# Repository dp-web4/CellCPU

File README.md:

# CellCPU Documentation

**ModBatt Battery Management System - Individual Cell Controller**

## Overview

The CellCPU is a **production-ready** foundational component of ModBatt's hierarchical battery management system, providing individual cell monitoring and control for lithium-ion battery applications. Each CellCPU manages a single cell with precision voltage monitoring, temperature sensing, and active balancing control.

**Implementation Status**: ✅ **Complete and functional** - All core modules implemented with sophisticated interrupt-driven architecture.

### Quick Facts

- **Target Platform**: ATtiny45 microcontroller (8-bit AVR)
- **Cell Interface**: Direct monitoring of single lithium-ion cell
- **Temperature Sensor**: MCP9843 precision digital sensor
- **Communication**: Virtual UART at 20kbps in daisy-chain topology
- **Power Consumption**: <1mA typical operation
- **Scalability**: Up to 128 CellCPUs per ModuleCPU

## Web4 Ecosystem Context

CellCPU is the foundational layer of a **trust-native battery management system** demonstrating [Web4](https://github.com/dp-web4/web4) principles in production embedded hardware:

**Philosophy**: [Synchronism](https://github.com/dp-web4/Synchronism) - Distributed intelligence and scale-based autonomy
**Standard**: [Web4](https://github.com/dp-web4/web4) - Trust-native internet architecture with LCTs and MRH
**Implementation**: **CellCPU** (this) → [ModuleCPU](https://github.com/dp-web4/ModuleCPU) → [Pack-Controller](https://github.com/dp-web4/Pack-Controller-EEPROM)

### Web4 Integration

Each CellCPU operates as an autonomous agent with:
- **LCT Identity**: Unforgeable blockchain binding via hardware serial number
- **Markov Blanket**: VUART interface hides internal complexity from ModuleCPU
- **Local Intelligence**: Autonomous decision-making (balancing, error detection)
- **Trust Tensors**: ModuleCPU tracks T3 (Talent/Training/Temperament) and V3 (Veracity/Validity/Value)
- **Witnessed Presence**: ModuleCPU witnesses cell existence via VUART communication

See [WEB4_INTEGRATION.md](WEB4_INTEGRATION.md) for complete Web4 architecture details.

### Synchronism Principles

CellCPU demonstrates cosmic-to-silicon philosophy:
- **Scale-Based Autonomy**: Cell makes local decisions within module context
- **Markov Blankets**: VUART interface defines cell's reality boundary
- **Distributed Intelligence**: No central cell controller - intelligence emerges from hierarchy
- **Sensor Fusion**: Temperature + voltage + time → emergent "cell health"
- **Intent Dynamics**: Battery charge/discharge as metabolic intent propagation

See [SYNCHRONISM_PRINCIPLES.md](SYNCHRONISM_PRINCIPLES.md) for philosophical depth.

### Ecosystem Links

- [Synchronism Whitepaper](https://github.com/dp-web4/Synchronism/blob/main/whitepaper.md) - Universal principles
- [Web4 Standard](https://github.com/dp-web4/web4/blob/main/web4-standard/README.md) - Internet standard
- [ModBatt Web4 Examples](https://github.com/dp-web4/web4/blob/main/docs/modbatt_implementation_examples.md) - Code walkthroughs

**This is not just a battery controller - it's proof that Web4 trust architecture works in 4KB of flash memory.**

---

## Documentation Structure

### 📖 Core Documentation

#### [System Overview](docs/overview/README.md)
Complete system overview, architecture, and integration context within the ModBatt ecosystem.

- System role and responsibilities
- Hardware platform specifications  
- Communication protocol overview
- Performance characteristics
- Integration with ModuleCPU and Pack Controller

#### [Software Architecture](docs/overview/architecture.md)
Detailed firmware architecture and design patterns.

- Event-driven state machine design
- Module organization and dependencies
- Memory management strategies
- Interrupt architecture
- Error handling and safety systems

### 🔧 Hardware Documentation

#### [Hardware Platform](docs/hardware/README.md)
Comprehensive hardware platform documentation covering the ATtiny45 microcontroller and supporting components.

- ATtiny45 specifications and capabilities
- Pin configuration and multiplexing
- External component integration
- Power system design
- PCB layout considerations
- Environmental specifications

### 💻 Firmware Documentation

#### [Firmware Architecture](docs/firmware/README.md)
Complete firmware module documentation and implementation details.

- Module hierarchy and interfaces
- ADC voltage measurement system
- Virtual UART communication implementation
- Temperature sensor integration
- Platform abstraction layer
- Build system and optimization

#### [Cell Interface & Monitoring](docs/cell-interface/README.md)
Detailed cell monitoring and control system documentation.

- Voltage monitoring with 10-bit ADC
- Temperature sensing via I2C
- Active balancing control
- Safety and protection features
- Calibration and accuracy optimization
- Diagnostic capabilities

### 🔗 Communication System

#### [Communication with ModuleCPU](docs/communication/README.md)
Complete communication protocol and implementation documentation.

- Physical layer implementation
- Message format and structure
- Daisy-chain topology management
- Virtual UART timing and control
- Error handling and recovery
- Performance optimization

#### [Temperature Sensing](docs/temperature/README.md)
Comprehensive temperature monitoring system documentation.

- MCP9843 sensor integration
- I2C communication interface
- Thermal management and control
- Pin multiplexing with ADC
- Calibration and accuracy
- Error handling and diagnostics

### 🛠️ Development

#### [Development Environment](docs/development/README.md)
Complete development environment setup and workflow documentation.

- Required software tools (Microchip Studio, XC8)
- Hardware setup and programming
- Build process and optimization
- Testing and validation procedures
- Version control workflow
- Best practices and standards

#### [Implementation Status](docs/implementation-status.md)
**NEW**: Comprehensive review of actual implementation completeness and quality.

- Complete module implementation status
- Code quality assessment
- Production readiness evaluation
- Hardware validation priorities
- Integration testing recommendations

## Quick Start Guide

### 1. Development Environment Setup

```bash
# Required Tools
1. Download and install Microchip Studio 7.0+
2. Install XC8 Compiler v2.36+
3. Setup Atmel-ICE programmer/debugger
4. Clone the CellCPU repository

# Open Project
1. Launch Microchip Studio
2. File → Open → Project/Solution
3. Select CellCPU.cproj
4. Build → Build Solution (F7)
```

### 2. Hardware Configuration

```c
// Key hardware connections
Pin Configuration:
├── PB0: cell_up_tx    (Output to upstream cell)
├── PB1: cell_dn_rx    (Input from downstream)
├── PB2: I2C SDA       (Temperature sensor)
├── PB3: I2C SCL/ADC3  (Temperature + voltage)
├── PB4: cell_up_rx    (Input from upstream)
└── PB5: cell_dn_tx    (Output to downstream)

Power: 3.0V to 5.5V (5.0V nominal)
Programming: 6-pin ISP header
```

### 3. Basic Usage

```c
// Actual implemented functionality
System Operation:
1. Interrupt-driven Virtual UART communication (20kbps)
2. Pin-multiplexed voltage (ADC) and temperature (I2C) sensing
3. MCP9843 EVENT pin control for discharge balancing
4. Sophisticated timer-based bit timing with guard bits
5. Automatic chain position detection and data relay
6. Robust I2C bit-banged implementation with ACK handling
7. Power-efficient ADC enable/disable cycling

// Core modules all implemented:
├── adc.c - Complete ADC implementation with power management
├── I2c.c - Full bit-banged I2C with timing quantization  
├── mcp9843.c - Complete temperature sensor driver
├── vUART.c - Sophisticated interrupt-driven communication
└── main.c - Complete state machine coordination
```

## Key Features

### 🔋 Cell Monitoring
- **Voltage**: 10-bit ADC with 1.1V reference, ~4.3mV resolution
- **Temperature**: MCP9843 sensor, ±0.5°C accuracy, 0.0625°C resolution
- **Range**: 2.0V-5.0V cell voltage, -40°C to +125°C temperature

### 📡 Communication
- **Protocol**: Custom serial over Virtual UART
- **Speed**: 20kbps (50μs bit time)
- **Topology**: Daisy-chain up to 128 cells
- **Latency**: <5ms per cell response time

### ⚡ Control & Safety
- **Balancing**: Active discharge via MCP9843 EVENT pin
- **Protection**: Voltage and temperature limit monitoring
- **Safety**: Fail-safe operation on communication loss
- **Power**: <1mA typical, <100μA idle

### 🎯 Performance
- **Memory**: 4KB Flash (62% used), 256B SRAM (58% used)
- **Real-time**: Interrupt-driven with timer-based precision timing
- **Communication**: Sophisticated Virtual UART with guard bits and relay
- **I2C Implementation**: Professional bit-banged with timing quantization
- **Power Management**: ADC power cycling, efficient pin multiplexing
- **Reliability**: Comprehensive error handling and recovery mechanisms

## System Integration

### ModBatt Architecture Context

```
Vehicle Control Unit (VCU)
    ↓ CAN Bus
Pack Controller (STM32WB55)
    ↓ CAN Bus
ModuleCPU (ATmega64M1) ←→ Up to 128 × CellCPU (ATtiny45)
    ↓                              ↓
Battery Module                Li-ion Cells
```

### Communication Flow

```
Command Flow (Downstream):
ModuleCPU → CellCPU(Last) → CellCPU(Middle) → CellCPU(First)

Data Flow (Upstream):  
ModuleCPU ← CellCPU(Last) ← CellCPU(Middle) ← CellCPU(First)
```

## Contributing

### Development Workflow

1. **Feature Development**: Create feature branch from `develop`
2. **Code Review**: Submit pull request with comprehensive testing
3. **Integration**: Merge to `develop` after approval
4. **Release**: Create release branch for final testing
5. **Production**: Merge to `main` and tag release

### Coding Standards

- **Style**: K&R brace style, 4-space indentation
- **Documentation**: Comprehensive function headers and inline comments
- **Testing**: Unit tests and integration validation required
- **Performance**: Memory and timing optimization mandatory

## License and Patents

### Software License

This software is licensed under the **GNU Affero General Public License v3.0 or later** (AGPL-3.0-or-later).

See [LICENSE](LICENSE) for full license text.
See [LICENSE_SUMMARY.md](LICENSE_SUMMARY.md) for a summary of software vs. hardware licensing.

### Patents

Protected by US Patents:
- **11,380,942**: Distributed battery management with autonomous cell controllers
- **11,469,470**: Hierarchical battery management architecture
- **11,575,270**: Related pack control systems

**Patent Grant**: A limited patent grant for the software is provided under the AGPL-3.0 license scope. See [PATENTS.md](PATENTS.md) for details.

**Hardware Licensing**: Separate from software. See `docs/legal/ModBatt_Product_License.pdf` for hardware manufacturing licensing.

### Copyright

© 2023-2025 Modular Battery Technologies, Inc.

**Open Source Release**: October 2025 - Part of the Web4 trust-native ecosystem demonstration.

## Support and Contact

For technical support, development questions, or collaboration opportunities:

- **Technical Documentation**: See individual module documentation
- **Development Issues**: Check troubleshooting sections in relevant docs
- **Hardware Support**: Refer to hardware platform documentation
- **Communication Protocol**: See communication system documentation

---

## Related Projects

This repository can be viewed as demonstrating patterns of distributed trust and verifiable provenance in embedded systems.

**Related**: [Web4](https://github.com/dp-web4/web4) (trust architecture) • [Synchronism](https://github.com/dp-web4/Synchronism) (conceptual framing)

---

**Note**: This documentation covers the CellCPU firmware component of the ModBatt battery management system. For complete system documentation, refer to the Pack Controller and ModuleCPU documentation.

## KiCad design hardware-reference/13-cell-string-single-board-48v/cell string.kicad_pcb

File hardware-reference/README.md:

# CellCPU Hardware Reference Designs

**Status**: Reference designs for educational and non-commercial use
**Patent Coverage**: Protected by US Patent 11,380,942 (Distributed battery management with autonomous cell controllers)
**Last Updated**: October 2025

---

## Overview

This directory contains reference hardware designs for implementing the CellCPU concept - an autonomous cell-level battery management controller based on ATtiny45. These designs demonstrate one possible hardware implementation of the patented distributed battery management architecture.

**Contents**:
- KiCad schematics and PCB layouts
- Bill of Materials (BOM)
- Manufacturing files

---

## Patent Coverage

These hardware designs implement concepts covered by multiple patents in the ModBatt patent portfolio:

### Complete Patent List

**Modular Battery Technologies, Inc. Patent Portfolio**:

1. **US 11,380,942** (PCT/US21/50518) - *High Voltage Battery Module with Series Connected Cells and Internal Relays*
   - Filed: November 2, 2020 | Issued: July 5, 2022
   - Module with series connected cells and relays

2. **US 11,469,470** (PCT/US21/53798) - *Battery Module with Series Connected Cells, Internal Relays and Internal Battery Management System*
   - Filed: January 4, 2021 | Issued: October 11, 2022
   - Cell monitoring/conditioning circuit, PCBAs, methods

3. **US 11,563,241** - *Apparatus and Methods for Removable Battery Module with Internal Relay and Internal Controller*
   - Filed: February 10, 2021 | Issued: December 14, 2022
   - Authentication methods and circuits

4. **US 11,575,270** (PCT/US21/55047) - *Battery Module with Series Connected Cells, Internal Relays and Internal Battery Management System*
   - Filed: February 22, 2021 (CIP) | Issued: February 7, 2023
   - AC coupled comms and methods

5. **US 11,699,817** (PCT/US21/54434) - *Apparatus and Methods for Removable Battery Module with Internal Relay and Internal Controller*
   - Filed: March 31, 2021 | Issued: July 11, 2023
   - System, pack and module controllers, blockchain

6. **US 11,477,027** (PCT/US21/55813) - *Apparatus and Methods for Management of Controlled Objects*
   - Filed: May 11, 2021 | Issued: October 18, 2022
   - Multi-domain management of controlled objects, LCT/blockchain

7. **US 11,936,008** (PCT/US21/60860) - *Electrical Power System with Removable Battery Modules*
   - Filed: November 17, 2021 | Issued: March 19, 2024
   - Dissimilar modules in parallel

8. **US 12,278,913** (PCT/US22/24797) - *Apparatus and Methods for Management of Controlled Objects*
   - Filed: March 31, 2022 | Issued: April 15, 2025
   - Linking of identifiable records

9. **US 11,876,250** (PCT/US22/xxx) - *High Voltage Battery Module with Series Connected Cells and Internal Relays*
   - Filed: May 31, 2022 | Issued: January 16, 2024
   - Dissimilar relays, PLC control bus, linear and PWM modes

10. **US 12,046,722** - *Electrical Power System with Removable Battery Modules*
    - Filed: December 12, 2022 | Issued: July 23, 2024
    - Vehicle and stationary installations having a power system, energizing a bus

11. **US 12,405,309** - *Low Cost Battery Cell Monitoring Circuit*
    - Filed: January 3, 2023 | Issued: September 2, 2025
    - Low cost ASIC

12. **US 12,136,739** - *Low Cost Battery Cell Monitoring Circuit*
    - Filed: December 14, 2023 | Issued: November 5, 2024
    - Low cost ASIC methods

13. **US 12,142,737** - *Electrical Power System with Removable Battery Modules*
    - Filed: December 14, 2023 | Issued: November 12, 2024

14. **US 18/935,265** - *High Voltage Battery Module with 1-Phase and 3-Phase AC Output*
    - Filed: November 1, 2024 | Status: Pending

**Assignee**: Modular Battery Technologies, Inc.
**Inventors**: Dennis Palatov, et al.

### Key Patented Concepts in CellCPU Hardware

- Cell-level autonomous controllers with local intelligence
- Virtual UART communication in daisy-chain topology
- Distributed temperature and voltage monitoring
- Markov blanket interface hiding internal cell complexity
- Low-cost cell monitoring circuits and ASICs
- Authentication methods for cell controllers

---

## License and Usage Terms

### Software License
The **CellCPU firmware** (parent directory) is licensed under **AGPL-3.0-or-later** with a patent grant for software use. See `../LICENSE` for details.

### Hardware Reference Designs
These hardware reference designs are provided under the following terms:

#### ✅ Permitted Uses (Non-Commercial Patent Grant)

You MAY use these designs **without a commercial hardware license** for:

1. **Educational Use**: Academic research, teaching, and learning
2. **Personal/Hobby Use**: Individual projects and experimentation
3. **Research & Development**: Prototyping and testing new concepts
4. **Open Source Development**: Contributing to AGPL-licensed software improvements

**Conditions**:
- No commercial sale or distribution of manufactured hardware
- Acknowledge patent and provide attribution
- Derivative works must include similar non-commercial use notice
- Software modifications must comply with AGPL-3.0-or-later

#### ❌ Restricted Uses (Requires Commercial License)

You MUST obtain a commercial hardware license from Modular Battery Technologies, Inc. for:

1. **Commercial Manufacturing**: Producing hardware for sale
2. **Commercial Products**: Incorporating designs into commercial battery products
3. **Revenue Generation**: Any use where hardware generates revenue directly or indirectly
4. **OEM Integration**: Selling products that include these designs

**Contact**: For commercial licensing inquiries, contact Modular Battery Technologies, Inc.

---

## Technical Scope

These reference designs demonstrate:

- **Cell Controller**: ATtiny45-based autonomous controller per cell
- **Temperature Sensing**: MCP9843 I²C temperature sensor integration
- **Virtual UART**: Software-based serial communication at 20kbps
- **Daisy-Chain Topology**: Up to 128 cells in series connection
- **Voltage Monitoring**: Per-cell voltage measurement architecture
- **Relay Control**: Cell bypass/isolation relay interface

**Voltage Range**: Designed for 13-cell strings (48V nominal LiFePO4)

---

## AS-IS Disclaimer and Limitations

### ⚠️ NO WARRANTY

**THESE HARDWARE REFERENCE DESIGNS ARE PROVIDED "AS IS" WITHOUT WARRANTY OF ANY KIND, EXPRESS OR IMPLIED, INCLUDING BUT NOT LIMITED TO THE WARRANTIES OF MERCHANTABILITY, FITNESS FOR A PARTICULAR PURPOSE, TITLE, AND NON-INFRINGEMENT.**

### Specific Disclaimers

1. **No Guarantee of Functionality**: These designs may contain errors, omissions, or may not function as intended
2. **No Safety Certification**: Designs have NOT been certified for safety (UL, CE, etc.)
3. **High Voltage Hazard**: Battery systems operate at dangerous voltages - **risk of electric shock, fire, explosion**
4. **Chemical Hazard**: Lithium battery failures can cause fire, toxic fumes, and explosions
5. **No Professional Engineering Review**: Use at your own risk - consult qualified professionals
6. **Rapidly Evolving**: These designs may be outdated or superseded

### 🚨 Battery Safety Warning

**DANGER**: Lithium-ion and LiFePO4 batteries are potentially hazardous.

- **Thermal runaway** can cause fires and explosions
- **Improper charging** can cause battery damage and fire
- **Short circuits** can cause severe burns and fire
- **Cell imbalance** can reduce lifespan and create safety hazards

**You are solely responsible for:**
- Proper safety engineering and testing
- Compliance with electrical codes and regulations
- Fire suppression and containment systems
- Proper charging and monitoring equipment
- Insurance and liability coverage

---

## Limitation of Liability

**IN NO EVENT SHALL MODULAR BATTERY TECHNOLOGIES, INC., ITS AFFILIATES, OR CONTRIBUTORS BE LIABLE FOR ANY DIRECT, INDIRECT, INCIDENTAL, SPECIAL, EXEMPLARY, OR CONSEQUENTIAL DAMAGES (INCLUDING, BUT NOT LIMITED TO, PROCUREMENT OF SUBSTITUTE GOODS OR SERVICES; LOSS OF USE, DATA, OR PROFITS; BUSINESS INTERRUPTION; PROPERTY DAMAGE; PERSONAL INJURY; OR DEATH) HOWEVER CAUSED AND ON ANY THEORY OF LIABILITY, WHETHER IN CONTRACT, STRICT LIABILITY, OR TORT (INCLUDING NEGLIGENCE OR OTHERWISE) ARISING IN ANY WAY OUT OF THE USE OF THESE DESIGNS, EVEN IF ADVISED OF THE POSSIBILITY OF SUCH DAMAGE.**

---

## Regulatory Compliance

### Your Responsibility

If you manufacture hardware based on these designs, YOU are responsible for:

1. **Electrical Safety**: UL/CSA/CE compliance as required
2. **FCC/EMC Compliance**: Radio frequency emissions and immunity
3. **Environmental**: RoHS, REACH, WEEE directives
4. **Transportation**: UN38.3 battery shipping requirements (if applicable)
5. **Local Codes**: Electrical codes and building codes in your jurisdiction

### No Compliance Warranty

**These designs have NOT been tested for regulatory compliance.** You must perform your own testing and certification.

---

## Design Files Information

### KiCad Version
Designs created with KiCad EDA (exact version in `.kicad_pro` files)

### File Structure
- `.kicad_sch` - Schematic files (hierarchical sheets)
- `.kicad_pcb` - PCB layout files
- `.csv` / `.ods` - Bill of Materials
- `mfg/` - Manufacturing output files (Gerbers, drill files, pick-and-place)

### Viewing and Editing
1. Download and install KiCad: https://www.kicad.org/
2. Open `.kicad_pro` project file
3. Libraries may need to be remapped on first open

---

## Attribution and Derivative Works

If you create derivative works based on these designs:

1. **Acknowledge the Source**:
   ```
   Based on CellCPU hardware reference designs
   Copyright (c) 2024-2025 Modular Battery Technologies, Inc.
   https://github.com/dp-web4/CellCPU
   ```

2. **Maintain Patent Notice**: Include reference to ModBatt patent portfolio (see Patent Coverage section)

3. **Propagate Non-Commercial Terms**: If distributing derivatives, include similar non-commercial use restrictions

4. **No Endorsement**: Do not imply that your derivative work is endorsed by Modular Battery Technologies, Inc.

---

## Support and Contributions

### No Support Commitment
These reference designs are provided without support. No assistance is guaranteed.

### Community Contributions
Improvements to these reference designs are welcome via pull requests:
- Clearly document changes and reasoning
- Maintain safety-critical design margins
- Include SPDX license headers if adding new files
- Sign-off on contributions (Developer Certificate of Origin)

---

## Relationship to Software License

**Key Distinction**:
- **Software (CellCPU firmware)**: AGPL-3.0-or-later with broad patent grant for software use
- **Hardware (these designs)**: Non-commercial patent grant only; commercial use requires separate license

**Why the Difference?**
- Software improvements benefit the ecosystem when shared (AGPL ensures sharing)
- Hardware manufacturing involves significant capital investment and safety liability
- Patent coverage primarily relates to hardware architecture and topology

**Can I modify the software for use on different hardware?**
- Yes! The AGPL-3.0 software license and patent grant apply to the software
- You can run modified CellCPU software on your own hardware implementations
- Commercial hardware sales still require a hardware patent license

---

## Questions?

**Technical Questions**: Open an issue on GitHub (https://github.com/dp-web4/CellCPU/issues)
**Commercial Licensing**: Contact Modular Battery Technologies, Inc.
**Safety Concerns**: Consult a qualified electrical engineer and safety professional

---

## Legal Summary

| **Aspect** | **Terms** |
|------------|-----------|
| **Software License** | AGPL-3.0-or-later (see `../LICENSE`) |
| **Hardware Designs** | Reference only - non-commercial patent grant |
| **Patents** | 14 US patents (1 pending) - commercial use requires license |
| **Warranty** | NONE - "AS IS" |
| **Liability** | User assumes all risk and liability |
| **Safety** | NOT certified - dangerous high voltage battery application |
| **Commercial Use** | Requires separate commercial license agreement |

---

**© 2024-2025 Modular Battery Technologies, Inc.**
**Patents**: 14 US patents covering battery management systems (see Patent Coverage section)
**Reference designs provided for educational and non-commercial use only**

---

*Last updated: October 2025*
*For latest terms, see https://github.com/dp-web4/CellCPU*

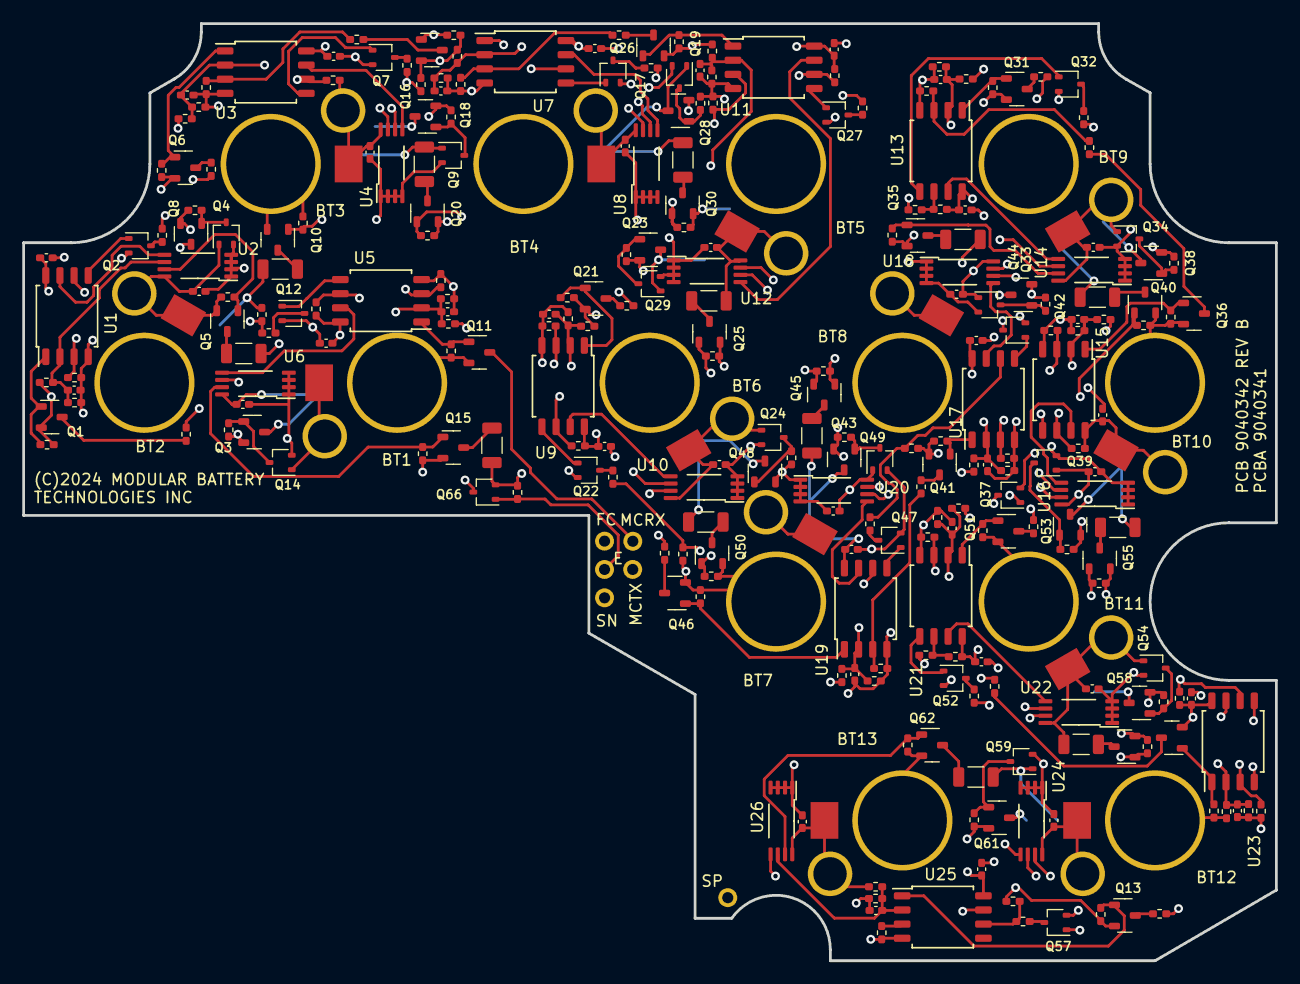
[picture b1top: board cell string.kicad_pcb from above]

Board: 4 copper layers, 112.5 x 84.2 mm, 275 parts (0 on the bottom side), 168 nets.

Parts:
BT1, BT2, BT3, BT4, BT5, BT6, BT7, BT8, BT9, BT10, BT11, BT12, BT13: Battery_Cell; modbatt cell new
C1, C3, C4, C6, C7, C9, C10, C12, C13, C15, C16, C18, C19, C21, C22, C24, C25, C27, C28, C30, C31, C33, C34, C36, C37, C39: .1uF; C_0402_1005Metric_Pad0.74x0.62mm_HandSolder
C2, C5, C8, C11, C14, C17, C20, C23, C26, C29, C32, C35, C38: 10pF; C_0402_1005Metric_Pad0.74x0.62mm_HandSolder
J1, J2, J3, J4, J5, J6: Conn_01x01_Pin; PinHeader_1x01_P1.00mm_Horizontal
Q1, Q3, Q5, Q6, Q8, Q10, Q11, Q13, Q15, Q16, Q18, Q20, Q21, Q23, Q25, Q26, Q28, Q30, Q31, Q33, Q35, Q36, Q38, Q40, Q41, Q43, Q45, Q46, Q48, Q50, Q51, Q53, Q55, Q56, Q58, Q60, Q61, Q62: DMP3099L-7-HXY; SOT-23
Q2, Q4, Q7, Q9, Q12, Q14, Q17, Q19, Q22, Q24, Q27, Q29, Q32, Q34, Q37, Q39, Q42, Q44, Q47, Q49, Q52, Q54, Q57, Q59, Q66: 2N7002; SOT-323_SC-70
R1, R2, R3, R4, R5, R8, R11, R12, R13, R14, R15, R18, R21, R22, R23, R24, R25, R31, R32, R33, R34, R35, R38, R41, R42, R43, R44, R45, R48, R51, R52, R53, R54, R55, R58, R61, R62, R63, R64, R65, R68, R71, R72, R73, R74, R75, R78, R81, R82, R83, R84, R85, R88, R91, R92, R93, R94, R95, R98, R101, R102, R103, R104, R105, R108, R111, R112, R113, R114, R115, R118, R121, R122, R131: 2.2K; R_0402_1005Metric_Pad0.72x0.64mm_HandSolder
R6, R16, R26, R36, R46, R56, R66, R76, R86, R96, R106, R116, R123: 90.9k 0.1%; R_0402_1005Metric_Pad0.72x0.64mm_HandSolder
R7, R17, R27, R37, R47, R57, R67, R77, R87, R97, R107, R117, R124: 30.1k 0.1%; R_0402_1005Metric_Pad0.72x0.64mm_HandSolder
R9, R19, R28, R29, R39, R49, R59, R69, R79, R89, R99, R109, R119, R125, R126: 4.7K; R_0402_1005Metric_Pad0.72x0.64mm_HandSolder
R10, R20, R30, R40, R50, R60, R70, R80, R90, R100, R110, R120, R127: 100; R_1206_3216Metric_Pad1.30x1.75mm_HandSolder
U1, U3, U5, U7, U9, U11, U13, U15, U17, U19, U21, U23, U25: ATtiny45V-10SU; SOIC-8W_5.3x5.3mm_P1.27mm
U2, U4, U6, U8, U10, U12, U14, U16, U18, U20, U22, U24, U26: MCP9843T-BE/ST; DFN-8-1EP_3x2mm_P0.5mm_EP1.36x1.46mm

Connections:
/CELL EN: J6.1, Q66.1 (G), R131.1
/FIRST CELL: BT1.1 (+), C7.1, C9.1, J5.1, Q3.3, Q11.2, Q14.1 (G), Q15.2, R10.2, R22.1, R25.1, R26.1, R29.1, U5.8 (VCC), U6.8 (V_{DD})
/MC RX: J4.1, Q11.3
/MC TX: J3.1, R25.2, U5.6 (PB1)
/STRING NEG: J2.1, Q66.2 (S), R30.2, R131.2
/STRING POS: BT13.1 (+), C37.1, C39.1, J1.1, Q13.2, Q62.2, R28.1, R122.1, R123.1, R126.1, U25.8 (VCC), U26.8 (V_{DD})
/cell circuit1/CMGND: C7.2, C8.2, C9.2, Q12.2 (S), Q14.2 (S), Q66.3 (D), R21.2, R27.2, U5.4 (GND), U6.1 (A0), U6.2 (A1), U6.3 (A2), U6.4 (GND)
/cell circuit1/DN TX/RST: Q11.1, R22.2, U5.1 (~RESET/PB5)
/cell circuit1/SCL/VCELL: C8.1, R26.2, R27.1, U5.2 (XTAL1/PB3), U6.6 (SCL)
/cell circuit1/SDA: U5.7 (PB2), U6.5 (SDA)
/cell circuit1/UP TX: Q12.1 (G), U5.5 (AREF/PB0)
/cell circuit1/cell up rx: R3.2, R21.1, U5.3 (XTAL2/PB4)
/cell circuit1/cell up tx: R5.2, R24.1, U1.6 (PB1)
/cell circuit1/cell_en out: Q3.1, Q14.3 (D), R8.2
/cell circuit2/CMGND: C1.2, C2.2, C3.2, Q2.2 (S), Q3.2, Q4.2 (S), R1.2, R7.2, R8.1, U1.4 (GND), U2.1 (A0), U2.2 (A1), U2.3 (A2), U2.4 (GND)
/cell circuit2/DN TX/RST: Q1.1, R2.2, U1.1 (~RESET/PB5)
/cell circuit2/SCL/VCELL: C2.1, R6.2, R7.1, U1.2 (XTAL1/PB3), U2.6 (SCL)
/cell circuit2/SDA: U1.7 (PB2), U2.5 (SDA)
/cell circuit2/UP TX: Q2.1 (G), U1.5 (AREF/PB0)
/cell circuit2/cell plus: BT2.1 (+), C1.1, C3.1, Q1.2, Q4.1 (G), Q5.2, Q8.3, R2.1, R5.1, R6.1, R9.1, R20.2, U1.8 (VCC), U2.8 (V_{DD})
/cell circuit2/cell up rx: R1.1, R13.2, U1.3 (XTAL2/PB4)
/cell circuit2/cell up tx: R4.1, R15.2, U3.6 (PB1)
/cell circuit2/cell_en out: Q4.3 (D), Q8.1, R18.2
/cell circuit3/CMGND: C4.2, C5.2, C6.2, Q7.2 (S), Q8.2, Q9.2 (S), R11.2, R17.2, R18.1, U3.4 (GND), U4.1 (A0), U4.2 (A1), U4.3 (A2), U4.4 (GND)
/cell circuit3/DN TX/RST: Q6.1, R12.2, U3.1 (~RESET/PB5)
/cell circuit3/SCL/VCELL: C5.1, R16.2, R17.1, U3.2 (XTAL1/PB3), U4.6 (SCL)
/cell circuit3/SDA: U3.7 (PB2), U4.5 (SDA)
/cell circuit3/UP TX: Q7.1 (G), U3.5 (AREF/PB0)
/cell circuit3/cell plus: BT3.1 (+), C4.1, C6.1, Q6.2, Q9.1 (G), Q10.2, Q18.3, R12.1, R15.1, R16.1, R19.1, R40.2, U3.8 (VCC), U4.8 (V_{DD})
/cell circuit3/cell up rx: R11.1, R33.2, U3.3 (XTAL2/PB4)
/cell circuit3/cell up tx: R14.1, R35.2, U7.6 (PB1)
/cell circuit3/cell_en out: Q9.3 (D), Q18.1, R38.2
/cell circuit4/CMGND: C10.2, C11.2, C12.2, Q17.2 (S), Q18.2, Q19.2 (S), R31.2, R37.2, R38.1, U7.4 (GND), U8.1 (A0), U8.2 (A1), U8.3 (A2), U8.4 (GND)
/cell circuit4/DN TX/RST: Q16.1, R32.2, U7.1 (~RESET/PB5)
/cell circuit4/SCL/VCELL: C11.1, R36.2, R37.1, U7.2 (XTAL1/PB3), U8.6 (SCL)
/cell circuit4/SDA: U7.7 (PB2), U8.5 (SDA)
/cell circuit4/UP TX: Q17.1 (G), U7.5 (AREF/PB0)
/cell circuit4/cell plus: BT4.1 (+), C10.1, C12.1, Q16.2, Q19.1 (G), Q20.2, Q28.3, R32.1, R35.1, R36.1, R39.1, R60.2, U7.8 (VCC), U8.8 (V_{DD})
/cell circuit4/cell up rx: R31.1, R53.2, U7.3 (XTAL2/PB4)
/cell circuit4/cell up tx: R34.1, R55.2, U11.6 (PB1)
/cell circuit4/cell_en out: Q19.3 (D), Q28.1, R58.2
/cell circuit5/CMGND: C16.2, C17.2, C18.2, Q27.2 (S), Q28.2, Q29.2 (S), R51.2, R57.2, R58.1, U11.4 (GND), U12.1 (A0), U12.2 (A1), U12.3 (A2), U12.4 (GND)
/cell circuit5/DN TX/RST: Q26.1, R52.2, U11.1 (~RESET/PB5)
/cell circuit5/SCL/VCELL: C17.1, R56.2, R57.1, U11.2 (XTAL1/PB3), U12.6 (SCL)
/cell circuit5/SDA: U11.7 (PB2), U12.5 (SDA)
/cell circuit5/UP TX: Q27.1 (G), U11.5 (AREF/PB0)
/cell circuit5/cell plus: BT5.1 (+), C16.1, C18.1, Q23.3, Q26.2, Q29.1 (G), Q30.2, R50.2, R52.1, R55.1, R56.1, R59.1, U11.8 (VCC), U12.8 (V_{DD})
/cell circuit5/cell up rx: R43.2, R51.1, U11.3 (XTAL2/PB4)
/cell circuit5/cell up tx: R45.2, R54.1, U9.6 (PB1)
/cell circuit5/cell_en out: Q23.1, Q29.3 (D), R48.2
/cell circuit6/CMGND: C13.2, C14.2, C15.2, Q22.2 (S), Q23.2, Q24.2 (S), R41.2, R47.2, R48.1, U9.4 (GND), U10.1 (A0), U10.2 (A1), U10.3 (A2), U10.4 (GND)
/cell circuit6/DN TX/RST: Q21.1, R42.2, U9.1 (~RESET/PB5)
/cell circuit6/SCL/VCELL: C14.1, R46.2, R47.1, U9.2 (XTAL1/PB3), U10.6 (SCL)
/cell circuit6/SDA: U9.7 (PB2), U10.5 (SDA)
/cell circuit6/UP TX: Q22.1 (G), U9.5 (AREF/PB0)
/cell circuit6/cell plus: BT6.1 (+), C13.1, C15.1, Q21.2, Q24.1 (G), Q25.2, Q48.3, R42.1, R45.1, R46.1, R49.1, R100.2, U9.8 (VCC), U10.8 (V_{DD})
/cell circuit6/cell up rx: R41.1, R93.2, U9.3 (XTAL2/PB4)
/cell circuit6/cell up tx: R44.1, R95.2, U19.6 (PB1)
/cell circuit6/cell_en out: Q24.3 (D), Q48.1, R98.2
/cell circuit7/CMGND: C28.2, C29.2, C30.2, Q47.2 (S), Q48.2, Q49.2 (S), R91.2, R97.2, R98.1, U19.4 (GND), U20.1 (A0), U20.2 (A1), U20.3 (A2), U20.4 (GND)
/cell circuit7/DN TX/RST: Q46.1, R92.2, U19.1 (~RESET/PB5)
/cell circuit7/SCL/VCELL: C29.1, R96.2, R97.1, U19.2 (XTAL1/PB3), U20.6 (SCL)
/cell circuit7/SDA: U19.7 (PB2), U20.5 (SDA)
/cell circuit7/UP TX: Q47.1 (G), U19.5 (AREF/PB0)
/cell circuit7/cell plus: BT7.1 (+), C28.1, C30.1, Q43.3, Q46.2, Q49.1 (G), Q50.2, R90.2, R92.1, R95.1, R96.1, R99.1, U19.8 (VCC), U20.8 (V_{DD})
/cell circuit7/cell up rx: R83.2, R91.1, U19.3 (XTAL2/PB4)
/cell circuit7/cell up tx: R85.2, R94.1, U17.6 (PB1)
/cell circuit7/cell_en out: Q43.1, Q49.3 (D), R88.2
/cell circuit8/CMGND: C25.2, C26.2, C27.2, Q42.2 (S), Q43.2, Q44.2 (S), R81.2, R87.2, R88.1, U17.4 (GND), U18.1 (A0), U18.2 (A1), U18.3 (A2), U18.4 (GND)
/cell circuit8/DN TX/RST: Q41.1, R82.2, U17.1 (~RESET/PB5)
/cell circuit8/SCL/VCELL: C26.1, R86.2, R87.1, U17.2 (XTAL1/PB3), U18.6 (SCL)
/cell circuit8/SDA: U17.7 (PB2), U18.5 (SDA)
/cell circuit8/UP TX: Q42.1 (G), U17.5 (AREF/PB0)
/cell circuit8/cell plus: BT8.1 (+), C25.1, C27.1, Q33.3, Q41.2, Q44.1 (G), Q45.2, R70.2, R82.1, R85.1, R86.1, R89.1, U17.8 (VCC), U18.8 (V_{DD})
/cell circuit8/cell up rx: R63.2, R81.1, U17.3 (XTAL2/PB4)
/cell circuit8/cell up tx: R65.2, R84.1, U13.6 (PB1)
/cell circuit8/cell_en out: Q33.1, Q44.3 (D), R68.2
/cell circuit9/CMGND: C19.2, C20.2, C21.2, Q32.2 (S), Q33.2, Q34.2 (S), R61.2, R67.2, R68.1, U13.4 (GND), U14.1 (A0), U14.2 (A1), U14.3 (A2), U14.4 (GND)
/cell circuit9/DN TX/RST: Q31.1, R62.2, U13.1 (~RESET/PB5)
/cell circuit9/SCL/VCELL: C20.1, R66.2, R67.1, U13.2 (XTAL1/PB3), U14.6 (SCL)
/cell circuit9/SDA: U13.7 (PB2), U14.5 (SDA)
/cell circuit9/UP TX: Q32.1 (G), U13.5 (AREF/PB0)
/cell circuit10/CMGND: C22.2, C23.2, C24.2, Q37.2 (S), Q38.2, Q39.2 (S), R71.2, R77.2, R78.1, U15.4 (GND), U16.1 (A0), U16.2 (A1), U16.3 (A2), U16.4 (GND)
/cell circuit10/DN TX/RST: Q36.1, R72.2, U15.1 (~RESET/PB5)
/cell circuit10/SCL/VCELL: C23.1, R76.2, R77.1, U15.2 (XTAL1/PB3), U16.6 (SCL)
/cell circuit10/SDA: U15.7 (PB2), U16.5 (SDA)
/cell circuit10/UP TX: Q37.1 (G), U15.5 (AREF/PB0)
/cell circuit10/cell dn rx: R64.1, R75.2, U15.6 (PB1)
/cell circuit10/cell dn tx: R61.1, R73.2, U13.3 (XTAL2/PB4)
/cell circuit10/cell minus: BT9.1 (+), C19.1, C21.1, Q31.2, Q34.1 (G), Q35.2, Q38.3, R62.1, R65.1, R66.1, R69.1, R80.2, U13.8 (VCC), U14.8 (V_{DD})
/cell circuit10/cell plus: BT10.1 (+), C22.1, C24.1, Q36.2, Q39.1 (G), Q40.2, Q53.3, R72.1, R75.1, R76.1, R79.1, R110.2, U15.8 (VCC), U16.8 (V_{DD})
/cell circuit10/cell up rx: R71.1, R103.2, U15.3 (XTAL2/PB4)
/cell circuit10/cell up tx: R74.1, R105.2, U21.6 (PB1)
/cell circuit10/cell_en in: Q34.3 (D), Q38.1, R78.2
/cell circuit10/cell_en out: Q39.3 (D), Q53.1, R108.2
/cell circuit11/CMGND: C31.2, C32.2, C33.2, Q52.2 (S), Q53.2, Q54.2 (S), R101.2, R107.2, R108.1, U21.4 (GND), U22.1 (A0), U22.2 (A1), U22.3 (A2), U22.4 (GND)
/cell circuit11/DN TX/RST: Q51.1, R102.2, U21.1 (~RESET/PB5)
/cell circuit11/SCL/VCELL: C32.1, R106.2, R107.1, U21.2 (XTAL1/PB3), U22.6 (SCL)
/cell circuit11/SDA: U21.7 (PB2), U22.5 (SDA)
/cell circuit11/UP TX: Q52.1 (G), U21.5 (AREF/PB0)
/cell circuit11/cell plus: BT11.1 (+), C31.1, C33.1, Q51.2, Q54.1 (G), Q55.2, Q58.3, R102.1, R105.1, R106.1, R109.1, R120.2, U21.8 (VCC), U22.8 (V_{DD})
/cell circuit11/cell up rx: R101.1, R113.2, U21.3 (XTAL2/PB4)
/cell circuit11/cell up tx: R104.1, R115.2, U23.6 (PB1)
/cell circuit11/cell_en out: Q54.3 (D), Q58.1, R118.2
/cell circuit12/CMGND: C34.2, C35.2, C36.2, Q57.2 (S), Q58.2, Q59.2 (S), R111.2, R117.2, R118.1, U23.4 (GND), U24.1 (A0), U24.2 (A1), U24.3 (A2), U24.4 (GND)
/cell circuit12/DN TX/RST: Q56.1, R112.2, U23.1 (~RESET/PB5)
/cell circuit12/SCL/VCELL: C35.1, R116.2, R117.1, U23.2 (XTAL1/PB3), U24.6 (SCL)
/cell circuit12/SDA: U23.7 (PB2), U24.5 (SDA)
/cell circuit12/UP TX: Q57.1 (G), U23.5 (AREF/PB0)
/cell circuit12/cell plus: BT12.1 (+), C34.1, C36.1, Q56.2, Q59.1 (G), Q60.2, Q61.3, R112.1, R115.1, R116.1, R119.1, R127.2, U23.8 (VCC), U24.8 (V_{DD})
/cell circuit12/cell up rx: R111.1, R121.2, U23.3 (XTAL2/PB4)
/cell circuit12/cell up tx: R114.1, R122.2, U25.6 (PB1)
/cell circuit12/cell_en out: Q59.3 (D), Q61.1, R125.2
/cell circuit13/CMGND: C37.2, C38.2, C39.2, Q61.2, R23.2, R124.2, R125.1, U25.4 (GND), U26.1 (A0), U26.2 (A1), U26.3 (A2), U26.4 (GND)
/cell circuit13/DN TX/RST: Q13.1, R28.2, U25.1 (~RESET/PB5)
/cell circuit13/SCL/VCELL: C38.1, R123.2, R124.1, U25.2 (XTAL1/PB3), U26.6 (SCL)
/cell circuit13/SDA: U25.7 (PB2), U26.5 (SDA)
unnamed: Q1.3, R3.1
unnamed: Q2.3 (D), R4.2
unnamed: Q5.3, R10.1
unnamed: Q6.3, R13.1
unnamed: Q7.3 (D), R14.2
unnamed: Q10.3, R20.1
unnamed: Q12.3 (D), R24.2
unnamed: Q13.3, R121.1
unnamed: Q15.3, R30.1
unnamed: Q16.3, R33.1
unnamed: Q17.3 (D), R34.2
unnamed: Q20.3, R40.1
unnamed: Q21.3, R43.1
unnamed: Q22.3 (D), R44.2
unnamed: Q25.3, R50.1
unnamed: Q26.3, R53.1
unnamed: Q27.3 (D), R54.2
unnamed: Q30.3, R60.1
unnamed: Q31.3, R63.1
unnamed: Q32.3 (D), R64.2
unnamed: Q35.3, R70.1
unnamed: Q36.3, R73.1
unnamed: Q37.3 (D), R74.2
unnamed: Q40.3, R80.1
unnamed: Q41.3, R83.1
unnamed: Q42.3 (D), R84.2
unnamed: Q45.3, R90.1
unnamed: Q46.3, R93.1
unnamed: Q47.3 (D), R94.2
unnamed: Q50.3, R100.1
unnamed: Q51.3, R103.1
unnamed: Q52.3 (D), R104.2
unnamed: Q55.3, R110.1
unnamed: Q56.3, R113.1
unnamed: Q57.3 (D), R114.2
unnamed: Q60.3, R120.1
unnamed: Q62.3, R127.1
unnamed: Q5.1, R9.2, U2.7 (Event)
unnamed: Q10.1, R19.2, U4.7 (Event)
unnamed: Q15.1, R29.2, U6.7 (Event)
unnamed: Q20.1, R39.2, U8.7 (Event)
unnamed: Q25.1, R49.2, U10.7 (Event)
unnamed: Q30.1, R59.2, U12.7 (Event)
unnamed: Q35.1, R69.2, U14.7 (Event)
unnamed: Q40.1, R79.2, U16.7 (Event)
unnamed: Q45.1, R89.2, U18.7 (Event)
unnamed: Q50.1, R99.2, U20.7 (Event)
unnamed: Q55.1, R109.2, U22.7 (Event)
unnamed: Q60.1, R119.2, U24.7 (Event)
unnamed: R23.1, U25.3 (XTAL2/PB4)
unnamed: Q62.1, R126.2, U26.7 (Event)

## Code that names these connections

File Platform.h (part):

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/*
 * Cell CPU definitions:
 *
 * PB0 - cell up tx
 * PB1 - cell dn rx
 * PB2 - I2C SDA
 * PB3 - I2C SDL/ADC1 (sense cell plus voltage through resistor divider)
 * PB4 - cell up rx
 * PB5 - cell dn tx (note: This has the net effect of inverting the signal between CPUs)
 *
 * Discharge is on the MPC9843T on the "event" pin. MCP9843T is at I2C addresses (A0-A2 are low):
 *
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
#define	INT_ENABLE()						GIMSK = (1 << PCIE); MCUCR = (MCUCR & ~3) | (1 << ISC00);	// Set to logical pin change interrupt - ensure INT0 isn't active

#define PIN_CELL_DN_RX						PB1
#define PIN_CELL_DN_RX_PORT					PORTB
#define PIN_CELL_DN_RX_DDR					DDRB
#define PIN_CELL_DN_RX_PIN					PINB
#define PIN_CELL_DN_RX_INT					PCINT1

#define PIN_CELL_UP_TX						PB0
#define PIN_CELL_UP_TX_PORT					PORTB
#define	PIN_CELL_UP_TX_DDR					DDRB
#define	PIN_CELL_UP_TX_PIN					PINB

#define PIN_CELL_UP_RX						PB4
#define	PIN_CELL_UP_RX_PORT					PORTB
#define PIN_CELL_UP_RX_DDR					DDRB
#define PIN_CELL_UP_RX_PIN					PINB
#define PIN_CELL_UP_RX_INT					PCINT4

#define PIN_CELL_DN_TX						PB5
#define PIN_CELL_DN_TX_PORT					PORTB
#define PIN_CELL_DN_TX_DDR					DDRB
#define PIN_CELL_DN_TX_PIN					PINB
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#define TIMER_CHB_INT_DISABLE()				TIMSK &= (uint8_t) ~(1 << OCIE0B)

// Profiling bits
// Using PB2 (I2C SDA) for profiling during VUART RX operations
// Pin is automatically switched between profiler (OUTPUT) and I2C (INPUT) modes
// by PROFILER_ENABLE_OUTPUT() / PROFILER_RESTORE_I2C() in vUART.c
#define PROFILER_INIT()						// No-op, pin configured on-demand
#define PROFILER_ENABLE_OUTPUT()			DDRB |= (1 << PORTB2)				// Configure PB2 as OUTPUT for profiler
#define PROFILER_RESTORE_I2C()				DDRB &= (uint8_t) ~(1 << PORTB2); PORTB |= (1 << PORTB2)	// Return to I2C SDA (INPUT with pullup)
#define PROF_1_ASSERT()						PORTB |= (1 << PORTB2)
#define PROF_1_DEASSERT()					PORTB &= (uint8_t) ~(1 << PORTB2)
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
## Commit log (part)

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2025-07-04 added claude documentation
    claude-generated docs
2025-07-28 added claude context
2025-09-13 feat(vuart): implement edge-triggered timing correction for VUART reception
    - Added edge correction for both upstream (cell_up_rx) and downstream (cell_dn_rx) reception
    - Tracks timing errors and applies corrections when drift exceeds tolerance
    - Keeps PCINT enabled during byte reception to detect bit edges
    - Uses same approach as proven in ModuleCPU
    - Should fix temperature data corruption (showing -55.35°C)
    The edge correction resynchronizes the sampling point to mid-bit position
2025-09-13 refactor(vuart): simplify edge correction to always resync
    - Removed conditional correction logic (TIMING_TOLERANCE, MAX_CORRECTION)
    - Now always resyncs timer on every edge, same as ModuleCPU
    - Keeps diagnostic tracking but simplifies the correction logic
    - More aggressive correction should better handle timing drift
2025-09-13 refactor(vuart): remove diagnostic tracking to save CPU cycles
    - Removed all timing error tracking variables and calculations
    - CellCPU has no debug capability due to restricted pin count
    - Keeps only the essential edge correction: resync timer on every edge
    - Saves CPU cycles and RAM on resource-constrained ATtiny45
2025-09-14 Fix VUART reception start timing for both channels
    - Fixed cell_up_rx: Now uses VUART_BIT_TICKS + (VUART_BIT_TICKS/2) - VUART_BIT_TICK_OFFSET
    - Fixed cell_dn_rx: Now uses VUART_BIT_TICKS + (VUART_BIT_TICKS/2) - VUART_BIT_TICK_OFFSET
    - Both channels now properly sample at middle of first data bit
    - Accounts for ISR response overhead with VUART_BIT_TICK_OFFSET
    - Matches corrected formula from ModuleCPU implementation
2025-09-19 Enable FAKE_CELL_DATA for testing
    Added #define FAKE_CELL_DATA to test with simulated cell data.
    Also removed VUART_BIT_TICKS from main.h as it's defined in Shared.h
2025-09-19 Disable FAKE_CELL_DATA - use real sensor data
2025-09-22 revert: remove edge sync from VUART to fix relay timing corruption
    Edge sync was causing variable bit widths in the relayed signal because
    the same timer controls both input sampling and output generation.
    Adjusting the timer for better reception corrupted the downstream
    transmission timing.
    Reverted to original fixed-timing approach that maintains consistent
    relay timing at the cost of occasional bit errors from clock drift.
2025-09-22 fix: correct date in edge sync revert comments (09/2025 not 12/2024)
2025-09-22 restore: vUART.c to original pre-edge-sync version
    Restoring to the initial known-good version from commit 7327a13.
    The edge sync experiments and revert remain in git history for reference.
    This gives us a clean baseline for any future improvements.
2025-09-23 refactor: use shared VUART timing constants from Shared.h
    - Moved ISR overhead compensation to Shared/Shared.h as VUART_ISR_OVERHEAD
    - Set to 0 for nominal timing (was 6 locally)
    - Added VUART_SAMPLE_OFFSET calculation in Shared.h
    - This allows consistent timing between CellCPU and ModuleCPU
    - Can be tuned empirically in one place for all projects
2025-09-28 Clean up git tracking - exclude build artifacts
    - Updated .gitignore to exclude all build files
    - Keep only .elf and .hex executables
    - Remove .o, .d, .map, .lss, .eep files from tracking
    - Remove Atmel Studio temp files (.atsuo, componentinfo.xml)
    - Remove backup files from tracking
2025-10-19 added hardware reference
2025-10-19 feat: Add academic citation and discoverability metadata
    - Add CITATION.cff with ORCID, keywords, patent identifiers
    - Add .github/TOPICS.md for GitHub topic suggestions
    - Include 20+ technical keywords for model scraper visibility
    - Link to Web4/Synchronism ecosystem references
    - Enable proper academic citation of software
    Enhances discoverability for researchers, model scrapers, academic databases.
2025-11-05 Move Shared headers to ModuleCPU and add VUART RX timing fix
    Step 1: Relocate Shared files to ModuleCPU/Shared
    - Copied Shared.h and protocol docs to ModuleCPU/Shared/
    - Shared/ is now tracked in ModuleCPU git repo instead of standalone
    Step 2: Update CellCPU include paths
    - Changed ../Shared/Shared.h to ../ModuleCPU/Shared/Shared.h
    - Modified: main.c, mcp9843.c, vUART.c

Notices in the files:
Platform.h:
(C) Copyright 2023-2024 Modular Battery Technologies, Inc.
hardware-reference/13-cell-string-single-board-48v/cell string.kicad_pcb:
(C)2023 modbatt
(C)2024 MODULAR BATTERY
